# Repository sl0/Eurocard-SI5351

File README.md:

# Eurocard-SI5351

This repo will contain an arduino sketch and KiCad files for a pcb.
The pcb shall output stable 25 and 40 MHz sine, derived from a 10MHz
OCXO or external GPSDO 10MHz

## Licenses

The arduino sketch is licensed under the terms of GNU General Public
License.

    https://www.gnu.org/licenses/#GPL

Files in the kicad directory are 'Open Source' under the terms of the
definition for Open Source Hardware Association.

    http://www.oshwa.org/definition/

## Arduino Sketch

A first sketch I got from Wolfram DF7KB, after he made some experiments
to reduce phase noise. The genious trick was to rely on integer
operations only in the synthesizer. It was derived from the examples 
found in 
[etherkit libraries][].

## KiCad files

The schema of the board is easy:

The routing of the pcb was done by hand:

    Have fun!

    sl0

[etherkit libraries]: https://github.com/etherkit/Si5351Arduino

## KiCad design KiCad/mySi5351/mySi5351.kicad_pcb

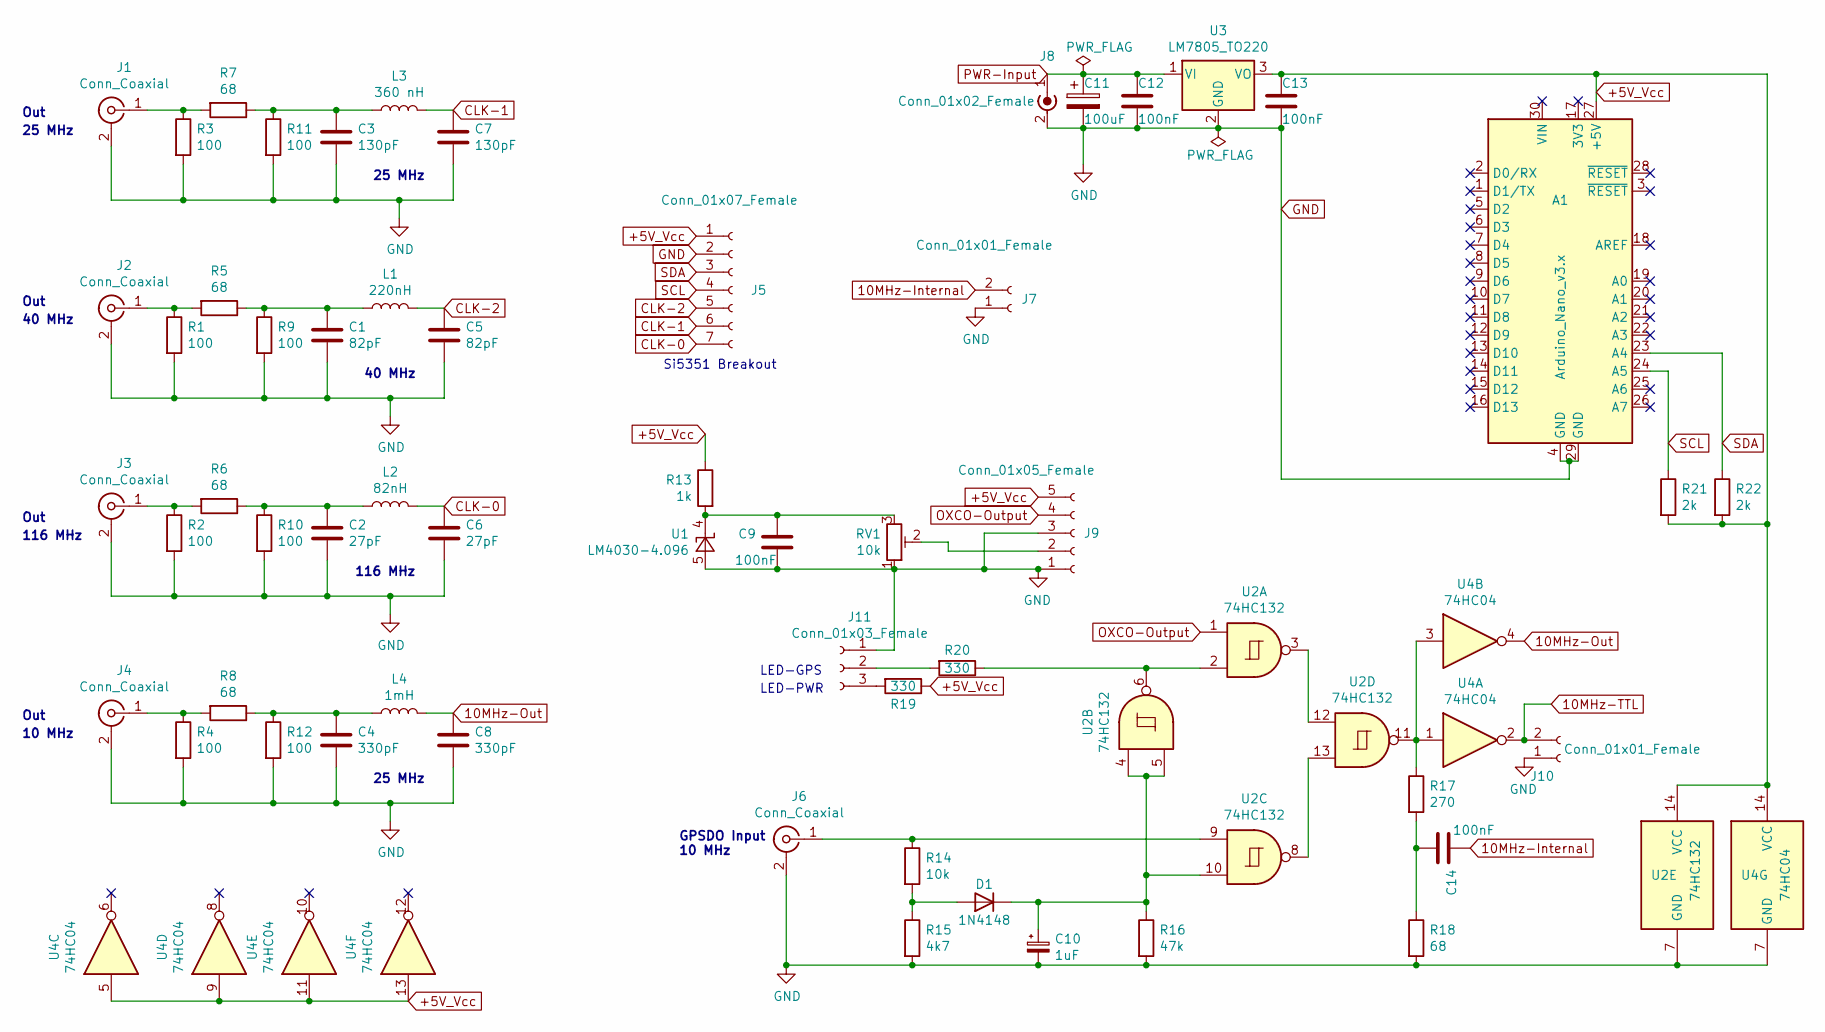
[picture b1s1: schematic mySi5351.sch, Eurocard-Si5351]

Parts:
A1: Arduino_Nano_v3.x; Arduino_Nano_WithMountingHoles
C1, C5: 82pF; C_1210_3225Metric_Pad1.33x2.70mm_HandSolder
C2, C6: 27pF; C_1210_3225Metric_Pad1.33x2.70mm_HandSolder
C3, C7: 130pF; C_1210_3225Metric_Pad1.33x2.70mm_HandSolder
C4, C8: 330pF; C_1210_3225Metric_Pad1.33x2.70mm_HandSolder
C9, C12, C13, C14: 100nF; C_1210_3225Metric_Pad1.33x2.70mm_HandSolder
C10: 1uF; CP_Elec_4x5.3
C11: 100uF; CP_Elec_8x10.5
D1: 1N4148; D_1210_3225Metric
J1, J2, J3, J4, J6: Conn_Coaxial; SMA_Molex_73251-1153_EdgeMount_Horizontal
J5: Conn_01x07_Female; PinHeader_1x07_P2.54mm_Vertical
J7, J10: Conn_01x01_Female; PinHeader_1x02_P2.54mm_Vertical
J8: Conn_01x02_Female; BarrelJack_Horizontal
J9: Conn_01x05_Female; PinHeader_1x05_P2.54mm_Vertical
J11: Conn_01x03_Female; PinHeader_1x03_P2.54mm_Vertical
L1: 220nH; L_1210_3225Metric_Pad1.42x2.65mm_HandSolder
L2: 82nH; L_1210_3225Metric_Pad1.42x2.65mm_HandSolder
L3: 360 nH; L_1210_3225Metric_Pad1.42x2.65mm_HandSolder
L4: 1mH; L_1210_3225Metric_Pad1.42x2.65mm_HandSolder
R1, R2, R3, R4, R9, R10, R11, R12: 100; R_1210_3225Metric_Pad1.30x2.65mm_HandSolder
R5, R6, R7, R8, R18: 68; R_1210_3225Metric_Pad1.30x2.65mm_HandSolder
R13: 1k; R_1210_3225Metric_Pad1.30x2.65mm_HandSolder
R14: 10k; R_1210_3225Metric_Pad1.30x2.65mm_HandSolder
R15: 4k7; R_1210_3225Metric_Pad1.30x2.65mm_HandSolder
R16: 47k; R_1210_3225Metric_Pad1.30x2.65mm_HandSolder
R17: 270; R_1210_3225Metric_Pad1.30x2.65mm_HandSolder
R19, R20: 330; R_1210_3225Metric_Pad1.30x2.65mm_HandSolder
R21, R22: 2k; R_1210_3225Metric_Pad1.30x2.65mm_HandSolder
RV1: 10k; Potentiometer_Bourns_3266P_Horizontal
U1: LM4030-4.096; SOT-23-5
U2: 74HC132; SO-14_3.9x8.65mm_P1.27mm
U3: LM7805_TO220; TO-220-3_Horizontal_TabDown
U4: 74HC04; SO-14_3.9x8.65mm_P1.27mm

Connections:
10MHz-Internal: C14.1, J7.2
10MHz-Out: C8.1, L4.2, U4.4
10MHz-TTL: J10.2, U4.2
+5V_Vcc: A1.27 (+5V), C13.1, J5.1, J9.5, R13.1, R19.1, R21.2, R22.2, U2.14 (VCC), U3.3 (VO), U4.5, U4.9, U4.11, U4.13, U4.14 (VCC)
CLK-0: C6.1, J5.7, L2.2
CLK-1: C7.1, J5.6, L3.2
CLK-2: C5.1, J5.5, L1.2
GND: A1.4 (GND), A1.29 (GND), C1.2, C2.2, C3.2, C4.2, C5.2, C6.2, C7.2, C8.2, C9.2, C10.2, C11.2, C12.2, C13.2, J1.2 (Ext), J2.2 (Ext), J3.2 (Ext), J4.2 (Ext), J5.2, J6.2 (Ext), J7.1, J8.2 (Ext), J9.1, J9.3, J10.1, J11.1, R1.2, R2.2, R3.2, R4.2, R9.2, R10.2, R11.2, R12.2, R15.2, R16.2, R18.2, RV1.1, U1.5 (A), U2.7 (GND), U3.2 (GND), U4.7 (GND)
unnamed: C1.1, L1.1, R5.1, R9.1
unnamed: C2.1, L2.1, R6.1, R10.1
unnamed: C3.1, L3.1, R7.1, R11.1
unnamed: C4.1, L4.1, R8.1, R12.1
unnamed: C9.1, R13.2, RV1.3, U1.4 (K)
unnamed: C10.1, D1.1 (K), R16.1, U2.4, U2.5, U2.10
unnamed: C14.2, R17.2, R18.1
unnamed: D1.2 (A), R14.2, R15.1
unnamed: J1.1 (In), R3.1, R7.2
unnamed: J2.1 (In), R1.1, R5.2
unnamed: J3.1 (In), R2.1, R6.2
unnamed: J4.1 (In), R4.1, R8.2
unnamed: J6.1 (In), R14.1, U2.9
unnamed: J9.2, RV1.2
unnamed: J11.2, R20.2
unnamed: J11.3, R19.2
unnamed: R17.1, U2.11, U4.1, U4.3
unnamed: R20.1, U2.2, U2.6
unnamed: U2.3, U2.12
unnamed: U2.8, U2.13
OXCO-Output: J9.4, U2.1
PWR-Input: C11.1, C12.1, J8.1 (In), U3.1 (VI)
SCL: A1.24 (A5), J5.4, R21.1
SDA: A1.23 (A4), J5.3, R22.1

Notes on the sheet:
Si5351 Breakout
GPSDO Input 10 MHz
25 MHz
40 MHz
116 MHz
10 MHz
Out
LED-GPS
LED-PWR

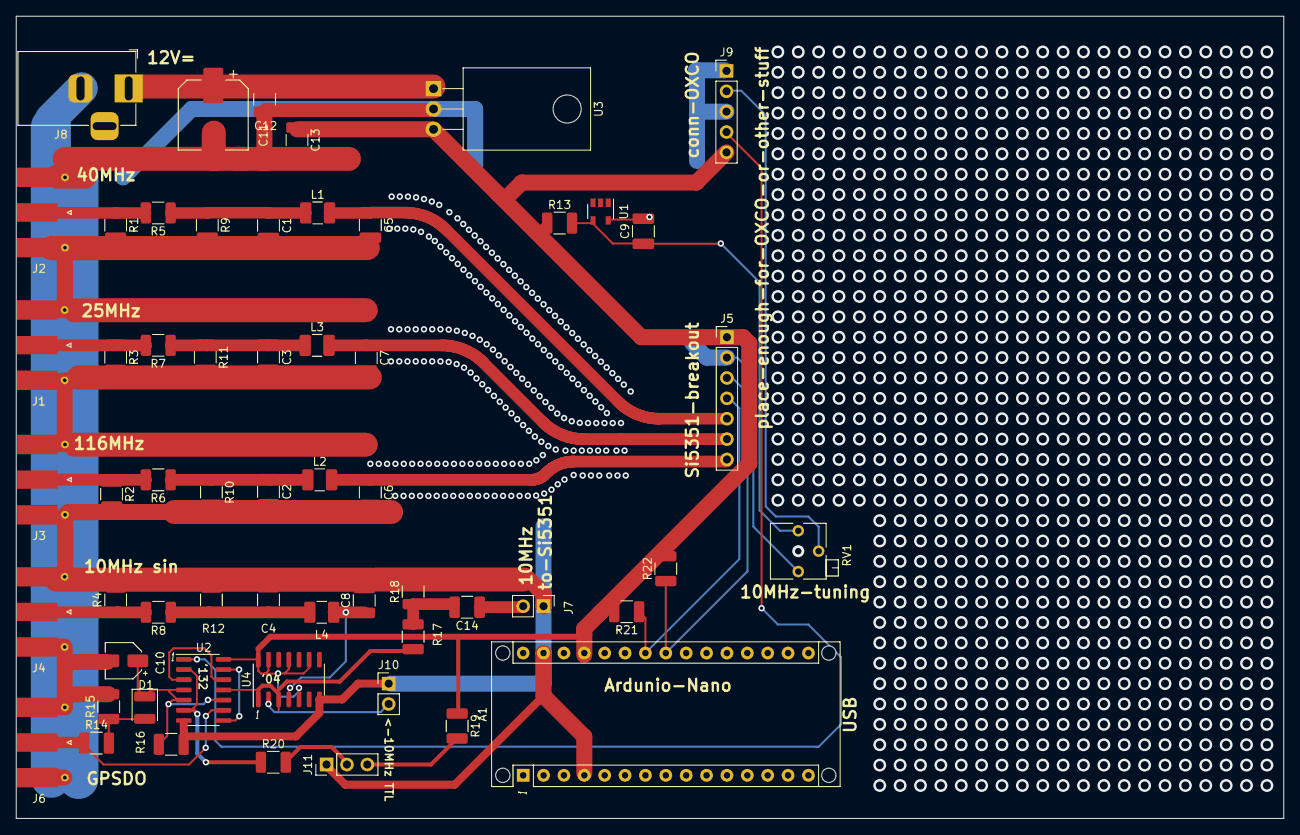
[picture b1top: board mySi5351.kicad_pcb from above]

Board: 2 copper layers, 158.0 x 100.0 mm, 58 parts (0 on the bottom side), 32 nets.

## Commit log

2020-11-29 Readme mentions licenses
    .gitignore useful complements Makefile, no products in the repo
2020-11-29 Adds first sketch in arduino-ide compatible directory
2020-11-29 Adds arduino-mk makefile
    updates .gitignore about products
2020-11-29 Adds schema and empty eurocard pcb
2020-11-29 Adds manual routes to pcb
    via grid and rounded traces looking well now
2020-11-29 Review, plotted files for first useable pcb
    The plots are products and send to factory, not included in repo
2020-11-29 Rewrites sketch, comments and sleep mode
2020-11-29 Adds pictures for your convienience
2020-12-04 Fixed a bug in schema, 100 instead of 10k Ohms

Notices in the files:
KiCad/mySi5351/mySi5351.kicad_pcb:
(c) 2020  DO1SLO
